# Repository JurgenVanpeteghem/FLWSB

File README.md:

# FLWSB
Flexible LoRaWAN Sensor Board - Hardware design

# Mistakes that were corrected
- In the previous version of the FLWSB the RX an TX lines were connected incorrectly to the LoraWan module. In the new version the RX and TX lines were connected correctly.
- In the previous version there was a mistake in the silkscreen. Pin "PA09" had to be "PA07". This mistake was corrected in the new version.

# Changes made to the board
- Three leds were added to the board. One led will indicate wheter the power supply is active. The other two leds were added on the RX and TX lines of the LoraWan module to indicate data transmission.
- Another type of voltage regulator was used on the new version. instead of the LD1117S33TR voltage regulator the LDL1117S33R was used in this version. The new voltage regulator has a wider range of input voltages and has a lower quiescent current.

# New schematic

# PCB

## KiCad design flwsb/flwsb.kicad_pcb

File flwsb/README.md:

# Flexible LoRaWAN Sensor Board SAMDaaNo21

Het FLWSB Main Board is een microcontroller bord gebaseerd op de ATSAM D21 in de vormfactor vergelijkbaar met een Arduino Nano. Het moet gemakkelijk zijn om dit bord in een breadboard te prikken en zo testen uit te voeren of schakelingen te bouwen. 

[PDF versie van de pinout diagram](./assets/SAMDaaNo21-pinout.pdf ':ignore')

## KiCad bibliotheken

Het is handig om een printplaat te kunnen ontwikkelen waar de SAMDaaNo21 opgeprikt kan worden.

Om dit proces te vergemakkelijken is er een KiCad bibliotheek ontwikkeld, die bevat een symbol, footprint en 3D-model.

Het is aangeraden om bibliotheken die niet standaard in KiCad zitten mee in de projectmap te steken en te importeren als projectbibliotheek. Als je je projectmap dan deelt met derden zullen zij meteen beschikken over alle nodige bibliotheken.

Tutorial: [How to import into KiCad V6 & later?](https://support.snapeda.com/en/articles/5995733-how-to-import-into-kicad-v6-later)

[SAMDaaNo21 bibliotheek bestanden](https://github.com/Dacetylan/FLWSB/tree/SAMDaaNo21/src/printed-circuit-boards/FLWSB-SAMDaaNo21-KiCad-lib)

## Schema

Het elektrisch schema van dit bord ziet er als volgt uit:

Alle onderdelen worden verder toegelicht.

[ATSAM D21 Datasheet](https://ww1.microchip.com/downloads/en/DeviceDoc/SAM-D21DA1-Family-Data-Sheet-DS40001882G.pdf)

## Testpunten

Er zijn verschillende testpunten toegevoegd om op een gemakkelijke en toegankelijke manier verschillende parameters op het bord te kunnen meten.

Er is gekozen voor through hole testpunten zodat het gemakkelijk is om deze met een probe te meten. Alle testpunten zijn te vinden nabij de USB-poort.

| Testpunt nummer | Verbinding                                                   |
| --------------- | ------------------------------------------------------------ |
| TP1             | VBUS: 5 V afkomstig van USB                                  |
| TP2             | VDD: 3,3 V gereguleerde spanning                              |
| TP3             | VIN: Ingangsspanning voordat het naar de lineaire regelaar gaat |

## LoRaWAN Module

Er is een RN2483 module mee geïmplementeerd op de printplaat. Deze is aangesloten op de UART bus van SERCOM 2.

De RN2483 bevindt zich aan het uiteinde. Er kan een antenne aangesloten worden via een U.FL connector.  

[Productpagina connector](https://be.farnell.com/hirose-hrs/u-fl-r-smt-1-10/rf-coaxial-u-fl-straight-jack/dp/1688077)

## USB Interface & VIN

Het schema voor de USB-interface is gebaseerd op een voorbeeld uit een Atmel handleiding. De zener diodes die zichtbaar zijn zorgen ervoor dat de kans op schade door elektrostatische ontlading (ESD) beperkt wordt.

[Ref USB-applications note](https://ww1.microchip.com/downloads/en/DeviceDoc/Atmel-42261-SAM-D21-USB_Application-Note_AT06475.pdf)

[Ref schematic checklist](https://ww1.microchip.com/downloads/en/DeviceDoc/SAM-D21DA1-Family-Data-Sheet-DS40001882G.pdf#_OPENTOPIC_TOC_PROCESSING_d10240e380866)

De Schottky diode (D6) is er om de USB-poort van je laptop te beschermen wanneer het bord van stroom wordt voorzien via de VIN pin. Het zou kunnen dat aan de VIN pin een hogere spanning wordt geleverd dan 5 V waardoor dit potentiaalverschil ongewenste stroom kan laten vloeien. Hetzelfde principe wordt toegepast bij de ESP32 DEVKIT.

`TP3` is een testpunt dat aanwezig is om op een toegankelijke manier de VIN-spanning te meten.

[Ref ESP32 schema](https://dl.espressif.com/dl/schematics/esp32_devkitc_v4-sch-20180607a.pdf)

Het bordje kan voorzien worden van stroom via de USB-C poort. Een LDO (Low Dropout regelaar) zal de spanning afkomstig van de computer reguleren naar een stabiele 3,3 V.

De LDO is een LD1117S33 en ondersteunt een minimale ingangsspanning van 4,3 V en een maximale van 15 V. Dat kan worden aangelegd via de VIN pin. Er is een Schottky diode voorzien om ervoor te zorgen dat de spanning van VIN niet op de USB-poort komt te staan.

*Let op dat je met een lineaire regelaar te maken hebt. Hoe hoger de ingangsspanning, hoe warmer de LDO zal worden!*

Het is ook mogelijk om de regelaar over te slaan en rechtstreeks 3,3 V te leveren via de 3V3 pin. Dit kan handig zijn bij een situatie waarin we zo zuinig mogelijk willen zijn en een efficiëntere 3,3 V regelaar gebruiken van een andere pcb. *Belangrijk is dat deze spanning niet te hard mag afwijken van 3,3 V!*

## RESET & DEBUG

De reset knop is opgebouwd zoals in de datasheet van de ATSAM D21 wordt weergegeven onder "Schematic Checklist Figure 45-4. External Reset Circuit Schematic".

Als er nog geen bootloader op de ATSAMD staat of als we een bare metal installatie gebruiken zullen we gebruik moeten maken van de program en debug header. Dat zijn de 3 pinnen centraal op de printplaat voor de LoRaWAN module. De pinout van links naar recht is: RESET, SWDIO, SWCLK. 

De ATSAMD maakt gebruik van Serial Wire Debugging (SWD), dat maakt het mogelijk om via fuses in te stellen, binaries in te laden en zelfs break-points aan je code toe te voegen.

## Low Dropout Lineair Regulator

In dit geval wordt er een LD1117 3,3 V regelaar gebruikt. Deze regelaar kan met een vrij groot ingangsbereik (tot 15 V) een uitgangsspanning van 3,3 V leveren.

`TP2` is een testpunt dat aanwezig is om op een toegankelijke manier de 3.3 V gereguleerde spanning te meten.

[LD1117 datasheet](https://www.st.com/resource/en/datasheet/ld1117.pdf)

## Power Supply Connections

Het schema voor de ontkoppelcondensatoren en spoel voor de ATSAM D21 komt ook rechtstreeks uit de datasheet. Wat belangrijk is bij deze componenten is dat alles rechts van de blauwe stippellijn zo dicht mogelijk bij de vermelde pinnen staat. Deze condensatoren vangen kleine storingen en rimpels op die zich voordoen in de bronspanning.

## Input / Output

Dit zijn alle GPIO, SERCOM en power aansluitingen die via pinheaders naar buiten worden gebracht. De SERCOM poorten zijn alvast gedefinieerd zodat onder andere de pull-up weerstanden geplaatst kunnen worden. Alle andere poorten zijn voor algemeen gebruik. In de datasheet van de ATSAM D21 onder 7. I/O Multiplexing and Considerations kunnen alle verschillende mogelijkheden van deze aansluitingen gevonden worden (AC, ADC, DAC, PTC, DAC, IO, ...).

PA12 en PA13 zijn onderdeel van de I²C bus en hebben al een pull-up weerstand van 4,7 K voorzien. *Bij het plaatsen van nog externe pull-up weerstanden zullen zij in parallel staan en zal de weerstandswaarde te laag worden.*

| I/O Pin | Pin      | SERCOM                  | SERCOM-ALT       | External Interrupt | ADC, DAC, AC, REF    | Peripheral Touch Controller | TC/TCC         | TCC            | COM               | Generic Clock Generator |
| ------- | -------- | ----------------------- | ---------------- | ------------------ | -------------------- | --------------------------- | -------------- | -------------- | ----------------- | ----------------------- |
| GND     | PowerPin | Ground Reference        |                  |                    |                      |                             |                |                |                   |                         |
| PA02    | 3        |                         |                  | EXTINT:2           | ADC:0<br/>VOUT       | Y:0                         |                | TCC3/<br/>WO:0 |                   |                         |
| PA03    | 4        |                         |                  | EXTINT:3           | ADC:1<br/>VREFA      | Y:1                         |                | TCC3/<br/>WO:1 |                   |                         |
| PB08    | 7        |                         | SCOM4/<br/>PAD:0 | EXTINT:8           | ADC:2                | Y:14                        | TC4/<br/>WO:0  | TCC3/<br/>WO:6 |                   |                         |
| PB09    | 8        |                         | SCOM4/<br/>PAD:1 | EXTINT:9           | ADC:3                | Y:15                        | TC4/<br/>WO:1  | TCC3/<br/>WO:7 |                   |                         |
| PA04    | 9        |                         | SCOM0/<br/>PAD:0 | EXTINT:4           | ADC:4<br/>AC:0 VREFB | Y:2                         | TCC0/<br/>WO:0 | TCC3/<br/>WO:2 |                   |                         |
| PA05    | 10       |                         | SCOM0/<br/>PAD:1 | EXTINT:5           | ADC:5<br/>AC:1       | Y:3                         | TCC0/<br/>WO:1 | TCC3/<br/>WO:3 |                   |                         |
| PA06    | 11       |                         | SCOM0/<br/>PAD:2 | EXTINT:6           | ADC:6<br/>AC:2       | Y:4                         | TCC1/<br/>WO:0 | TCC3/<br/>WO:4 |                   |                         |
| PA07    | 12       |                         | SCOM0/<br/>PAD:3 | EXTINT:7           | ADC:7<br/>AC:3       | Y:5                         | TCC1/<br/>WO:1 | TCC3/<br/>WO:5 | I2S/<br/>SD:0     |                         |
| PA08    | 13       | SCOM0/<br/>PAD:0        | SCOM2/<br/>PAD:0 | NMI                | ADC:16               | X:0                         | TCC0/<br/>WO:0 | TCC1/<br/>WO:2 | I2S/<br/>SD:1     |                         |
| PA09    | 14       | SCOM0/<br/>PAD:1        | SCOM2/<br/>PAD:1 | EXTINT:9           | ADC:17               | X:1                         | TCC0/<br/>WO:1 | TCC1/<br/>WO:3 | I2S/<br/>MCK:0    |                         |
| PA10    | 15       | SCOM0/<br/>PAD:2        | SCOM2/<br/>PAD:2 | EXTINT:10          | ADC:18               | X:2                         | TCC1/<br/>WO:0 | TCC0/<br/>WO:2 | I2S/<br/>SCK:0    | GCLK:4                  |
| PA11    | 16       | SCOM0/<br/>PAD:3        | SCOM2/<br/>PAD:3 | EXTINT:11          | ADC:19               | X:3                         | TCC1/<br/>WO:1 | TCC0/<br/>WO:3 | I2S/<br/>FS:0     | GCLK:5                  |
| PA12    | 21       | SCOM2/<br/>PAD:0        | SCOM4/<br/>PAD:0 | EXTINT:12          | AC:0                 |                             | TCC2/<br/>WO:0 | TCC0/<br/>WO:6 |                   |                         |
| PA13    | 22       | SCOM2/<br/>PAD:1        | SCOM4/<br/>PAD:1 | EXTINT:13          | AC:1                 |                             | TCC2/<br/>WO:1 | TCC0/<br/>WO:7 |                   |                         |
| VIN     | PowerPin | LDL1117S33 4.3 V - 15 V |                  |                    |                      |                             |                |                |                   |                         |
| 3V3     | PowerPin | 3.3V LDO output         |                  |                    |                      |                             |                |                |                   |                         |
| GND     | PowerPin | Ground Reference        |                  |                    |                      |                             |                |                |                   |                         |
| PB03    | 48       |                         | SCOM5/<br/>PAD:1 | EXTINT:3           | ADC:11               | Y:9                         | TC6/<br/>WO:1  | TCC3/<br/>WO:3 |                   |                         |
| PB22    | 37       |                         | SCOM5/<br/>PAD:2 | EXTINT:6           |                      |                             | TC7/<br/>WO:0  | TCC3/<br/>WO:0 |                   | GCLK:0                  |
| PA23    | 32       | SCOM3/<br/>PAD:1        | SCOM5/<br/>PAD:1 | EXTINT:7           |                      | X:11                        | TC4/<br/>WO:0  | TCC0/<br/>WO:5 | USB/<br/>SOF 1KhZ | GCLK:7                  |
| PA22    | 31       | SCOM3/<br/>PAD:0        | SCOM5/<br/>PAD:0 | EXTINT:6           |                      | X:10                        | TC4/<br/>WO:1  | TCC0/<br/>WO:4 |                   | GCLK:6                  |
| PA21    | 30       | SCOM5/<br/>PAD:3        | SCOM3/<br/>PAD:3 | EXTINT:5           |                      | X:9                         | TC7/<br/>WO:1  | TCC0/<br/>WO:7 | I2S/<br/>FS:0     | GCLK:5                  |
| PA20    | 29       | SCOM5/<br/>PAD:2        | SCOM3/<br/>PAD:2 | EXTINT:4           |                      | X:8                         | TC7/<br/>WO:0  | TCC0/<br/>WO:6 | I2S/<br/>SCK:0    | GCLK:4                  |
| PA19    | 28       | SCOM1/<br/>PAD:3        | SCOM3/<br/>PAD:3 | EXTINT:3           | AC:1                 | X:7                         | TC3/<br/>WO:1  | TCC0/<br/>WO:3 | I2S/<br/>SD:0     |                         |
| PA18    | 27       | SCOM1/<br/>PAD:2        | SCOM3/<br/>PAD:2 | EXTINT:2           | AC:0                 | X:6                         | TC3/<br/>WO:0  | TCC0/<br/>WO:2 |                   |                         |
| PA17    | 26       | SCOM1/<br/>PAD:1        | SCOM3/<br/>PAD:1 | EXTINT:1           |                      | X:5                         | TCC2/<br/>WO:1 | TCC0/<br/>WO:7 |                   | GCLK:3                  |
| PA16    | 25       | SCOM1/<br/>PAD:0        | SCOM3/<br/>PAD:0 | EXTINT:0           |                      | X:4                         | TCC2/<br/>WO:0 | TCC0/<br/>WO:6 |                   | GCLK:2                  |
| PA15    | 24       | SCOM2/<br/>PAD:3        | SCOM4/<br/>PAD:3 | EXTINT:15          |                      |                             | TC3/<br/>WO:1  | TCC0/<br/>WO:5 |                   | GCLK:1                  |
| PA14    | 23       | SCOM2/<br/>PAD:2        | SCOM4/<br/>PAD:2 | EXTINT:14          |                      |                             | TC3/<br/>WO:0  | TCC0/<br/>WO:4 |                   | GCLK:0                  |

### Legende

`SERCOM`: Serial Communication, keuze tussen: USART, I²C, SPI of SMBus

`EXTINT[n]`: External Interrupts

`AIN[n]`: ADC Analog Inputs

`X[n]`, `Y[n]`: Peripheral Touch Controller - PTC Input

`TC4/WO[n]`, `TC6/WO[n]`: Waveform/PWM Outputs

`TCC3/WO[n]`: Waveform/PWM Outputs/ Capture Inputs

`AC/CMP[n]`: AC Comparator Outputs

`I2S/FS[n]`: Inter-IC Sound Controller, I²S Word Select or TDM Frame Sync

`GCLK_IO[n]`: Generic Clock (source clock or generic clock generator output)

## Toekomstige verbeteringen

- Momenteel zijn er geen mounting holes aanwezig, dat vonden we  nog niet prioritair.
  - Mouning holes of inkepingen aan de randen van de printplaat zijn dus nog mogelijk en kunnen ook zeker van pas komen.
- De impedantie van het pad naar de antenne-aansluiting is niet theoretisch berekend. Dit is iets waar in een volgende versie over kan worden nagedacht.
- Er is geen LED aanwezig.
- Op het silkscreen staat een fout, `PA07` staat op het silkscreen als `PA09`. 
- Het schema bevat een fout die de LoRaWAN module onbruikbaar maakt. RX en TX van de UART-verbinding moeten omgewisseld worden.
  
### Tijdelijke oplossing LoRaWAN module

Een UART-verbinding heeft een TX (transmit) en RX (receive) aansluiting nodig. Logischerwijze zal je dus, bij een verbinding tussen twee apparaten, RX en TX met elkaar verbinden. Bij het ontwerpen van dit schema is door onoplettendheid TX met TX verbonden en RX met RX verbonden.

De PINMUX van de ATSAM D21 kan iedere SERCOM pin als RX instellen, maar niet iedere pin als TX schakelen. Dit maakt het onmogelijk om de oplossing geheel softwarematig te zoeken. Enkel PAD0 en PAD2 van een SERCOM poort kan je instellen als TX.

Wij hebben `PA8` (`S2TX` op het silkscreen) ingesteld als RX omdat deze verbonden is met de TX van de LoRaWAN module. `PA09` (`S2RX` op het silkscreen) hebben we hoog impedant gezet (`INPUT`) en kortgesloten met `PA10`. `PA10` is PAD2 van SERCOM2 dus kan ingesteld worden als nieuwe TX.

Het resultaat is dat we nu het baantje naar de RESET pin van de LoRaWAN module moeten onderbreken, omdat `PA10` verbonden is met deze pin. Die onderbreking is het gemakkelijkste te maken met een mesje of platte schroevendraaier net op de plek waar deze richting het pad van de module gaat.

De aanpassingen van deze pinnen is gemaakt in de ArduinoCore dus er hoeft in de code niets gewijzigd te worden.

Er is geen manier meer om de module te resetten vanaf de MCU, moest dat nodig zijn, dan kan er een kabeltje gesoldeerd worden naar een van de vrije GPIO pinnen.

## Bill of Materials

[Bill of materials ibom](./bom/ibom.html ':include :type=iframe width=100% height=1024px')

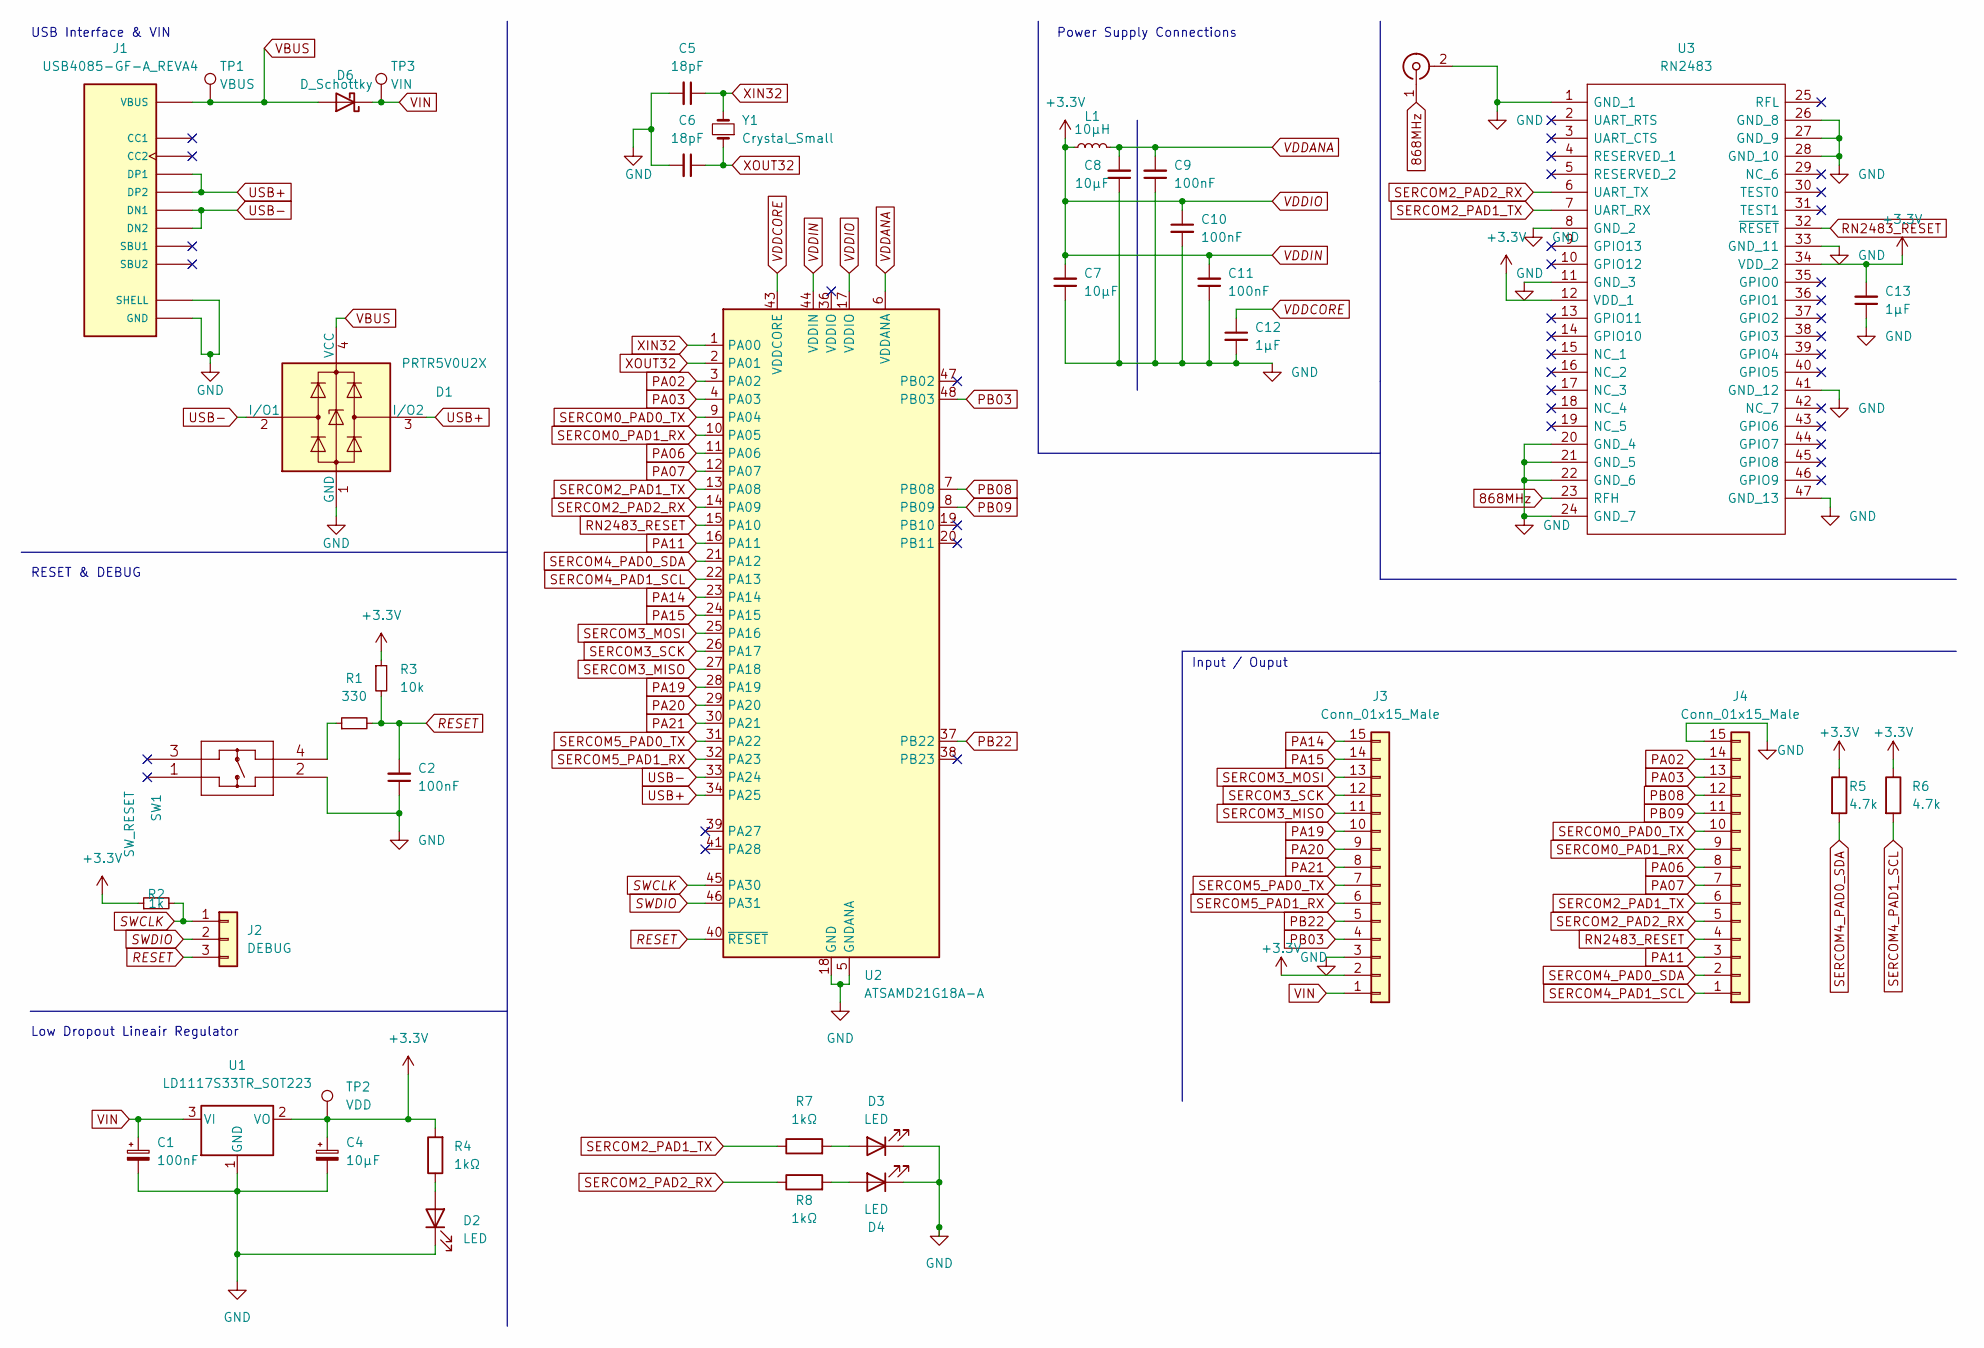
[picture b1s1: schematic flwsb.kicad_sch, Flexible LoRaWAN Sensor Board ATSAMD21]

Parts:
C1, C2, C9, C10, C11: 100nF; C_0805_2012Metric_Pad1.18x1.45mm_HandSolder
C4, C7, C8: 10µF; C_0805_2012Metric_Pad1.18x1.45mm_HandSolder
C5, C6: 18pF; C_0805_2012Metric_Pad1.18x1.45mm_HandSolder
C12, C13: 1µF; C_0805_2012Metric_Pad1.18x1.45mm_HandSolder
D1: PRTR5V0U2X; SOT-143
D2, D3, D4: LED; LED_0805_2012Metric_Pad1.15x1.40mm_HandSolder
D6: D_Schottky; SOD-123FL
J1: USB4085-GF-A_REVA4; GCT_USB4085-GF-A_REVA4; PARTREV A4
J2: DEBUG; PinHeader_1x03_P2.54mm_Vertical
J3, J4: Conn_01x15_Male; PinHeader_1x15_P2.54mm_Vertical
J6: Conn_Coaxial; U.FL_Molex_MCRF_73412-0110_Vertical
L1: 10µH; L_Murata_LQH2MCNxxxx02_2.0x1.6mm
R1: 330; R_0805_2012Metric_Pad1.20x1.40mm_HandSolder
R2: 1k; R_0805_2012Metric_Pad1.20x1.40mm_HandSolder
R3: 10k; R_0805_2012Metric_Pad1.20x1.40mm_HandSolder
R4, R7, R8: 1kΩ; R_0805_2012Metric_Pad1.20x1.40mm_HandSolder
R5, R6: 4.7k; R_0805_2012Metric_Pad1.20x1.40mm_HandSolder
SW1: SW_RESET; KMR7_CNK
TP1: VBUS; TestPoint_THTPad_1.0x1.0mm_Drill0.5mm
TP2: VDD; TestPoint_THTPad_1.0x1.0mm_Drill0.5mm
TP3: VIN; TestPoint_THTPad_1.0x1.0mm_Drill0.5mm
U1: LD1117S33TR_SOT223; SOT-223-3_TabPin2
U2: ATSAMD21G18A-A; TQFP-48_7x7mm_P0.5mm
U3: RN2483; Manufacturer_Part_Number RN2483
Y1: Crystal_Small; Crystal_SMD_3215-2Pin_3.2x1.5mm

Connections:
868MHz: J6.1 (In), U3.23 (RFH)
GND: C1.2, C2.1, C4.2, C5.2, C6.2, C7.1, C8.1, C9.1, C10.2, C11.1, C12.2, C13.1, D1.1 (GND), D2.1 (K), D3.1 (K), D4.1 (K), J1.A1 (GND), J1.A12 (GND), J1.B1 (GND), J1.B12 (GND), J1.P1 (SHELL), J1.P2 (SHELL), J1.P3 (SHELL), J1.P4 (SHELL), J3.3, J4.15, J6.2 (Ext), SW1.2, U1.1 (GND), U2.5 (GNDANA), U2.18 (GND), U2.35 (GND), U2.42 (GND), U3.1 (GND_1), U3.8 (GND_2), U3.11 (GND_3), U3.20 (GND_4), U3.21 (GND_5), U3.22 (GND_6), U3.24 (GND_7), U3.26 (GND_8), U3.27 (GND_9), U3.28 (GND_10), U3.33 (GND_11), U3.41 (GND_12), U3.47 (GND_13); also elsewhere on the board
unnamed: D2.2 (A), R4.1
unnamed: D3.2 (A), R7.2
unnamed: D4.2 (A), R8.2
unnamed: R1.1, SW1.4
PA02: J4.14, U2.3 (PA02)
PA03: J4.13, U2.4 (PA03)
PA06: J4.8, U2.11 (PA06)
PA07: J4.7, U2.12 (PA07)
PA11: J4.3, U2.16 (PA11)
PA14: J3.15, U2.23 (PA14)
PA15: J3.14, U2.24 (PA15)
PA19: J3.10, U2.28 (PA19)
PA20: J3.9, U2.29 (PA20)
PA21: J3.8, U2.30 (PA21)
PB03: J3.4, U2.48 (PB03)
PB08: J4.12, U2.7 (PB08)
PB09: J4.11, U2.8 (PB09)
PB22: J3.5, U2.37 (PB22)
RESET: C2.2, J2.3, R1.2, R3.2, U2.40 (~RESET)
RN2483_RESET: J4.4, U2.15 (PA10), U3.32 (~RESET)
SERCOM0_PAD0_TX: J4.10, U2.9 (PA04)
SERCOM0_PAD1_RX: J4.9, U2.10 (PA05)
SERCOM2_PAD1_TX: J4.6, R7.1, U2.13 (PA08), U3.7 (UART_RX)
SERCOM2_PAD2_RX: J4.5, R8.1, U2.14 (PA09), U3.6 (UART_TX)
SERCOM3_MISO: J3.11, U2.27 (PA18)
SERCOM3_MOSI: J3.13, U2.25 (PA16)
SERCOM3_SCK: J3.12, U2.26 (PA17)
SERCOM4_PAD0_SDA: J4.2, R5.2, U2.21 (PA12)
SERCOM4_PAD1_SCL: J4.1, R6.2, U2.22 (PA13)
SERCOM5_PAD0_TX: J3.7, U2.31 (PA22)
SERCOM5_PAD1_RX: J3.6, U2.32 (PA23)
SWCLK: J2.1, R2.2, U2.45 (PA30)
SWDIO: J2.2, U2.46 (PA31)
USB+: D1.3 (I/O2), J1.A6 (DP1), J1.B6 (DP2), U2.34 (PA25)
USB-: D1.2 (I/O1), J1.A7 (DN1), J1.B7 (DN2), U2.33 (PA24)
VBUS: D1.4 (VCC), D6.2 (A), J1.A4 (VBUS), J1.A9 (VBUS), J1.B4 (VBUS), J1.B9 (VBUS), TP1.1
VDDANA: C8.2, C9.2, L1.2, U2.6 (VDDANA)
VDDCORE: C12.1, U2.43 (VDDCORE)
VDDIN: C4.1, C7.2, C10.1, C11.2, C13.2, J3.2, L1.1, R2.1, R3.1, R4.2, R5.1, R6.1, TP2.1, U1.2 (VO), U2.17 (VDDIO), U2.44 (VDDIN), U3.12 (VDD_1), U3.34 (VDD_2)
VIN: C1.1, D6.1 (K), J3.1, TP3.1, U1.3 (VI)
XIN32: C5.1, U2.1 (PA00), Y1.2; also elsewhere on the board
XOUT32: C6.1, U2.2 (PA01), Y1.1

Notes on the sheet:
Power Supply Connections
Input / Ouput
Low Dropout Lineair Regulator
RESET & DEBUG
USB Interface & VIN

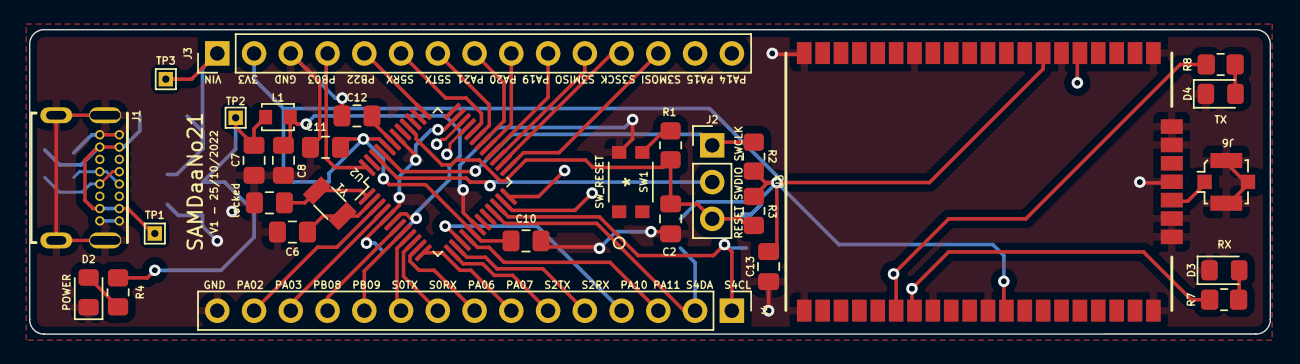
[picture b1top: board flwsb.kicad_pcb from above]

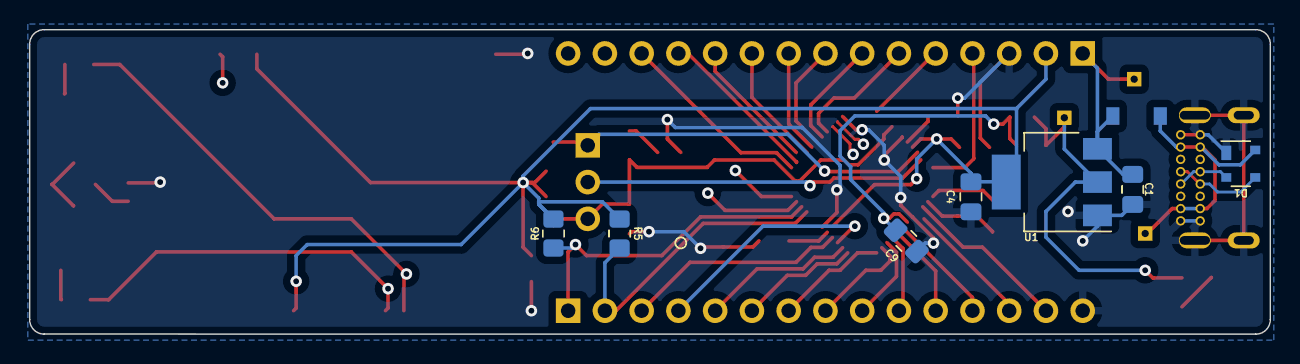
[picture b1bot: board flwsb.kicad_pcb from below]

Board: 4 copper layers, 85.7 x 21.0 mm, 39 parts (8 on the bottom side), 44 nets.

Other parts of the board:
locked: 18pF; C_0805_2012Metric_Pad1.18x1.45mm_HandSolder

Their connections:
GND: locked.2; also elsewhere on the board
XIN32: locked.1; also elsewhere on the board

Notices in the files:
parts and their libraries:
Copyright 2021 Accelerated Designs. All rights reserved.
